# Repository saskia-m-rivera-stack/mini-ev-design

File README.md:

# mini-ev-design
Custom PCB design for a mini, remote-control electric car

Overview

The Mini Electric Vehicle (EV) Platform is a compact, battery-powered robotics platform designed to demonstrate embedded systems, motor control, and PCB design concepts. The project uses an ESP32 microcontroller and a DRV8833 dual H-bridge motor driver to control a brushed DC motor from a rechargeable LiPo battery.

This project was designed in KiCad as a custom PCB and serves as a learning platform for:

DC motor control using PWM
H-bridge motor drivers
Battery-powered embedded systems
Power distribution and decoupling
Wireless control using ESP32 Wi-Fi or Bluetooth
PCB schematiclayout

Features
ESP32-based control system
DRV8833 motor driver
Single brushed DC motor support
3.7V LiPo battery operation
On-board power regulation
Reverse polarity protection
Fuse protection
Decoupling and bulk capacitance for power stability
Expandable for sensors and remote-control functionality

System Architecture
Power System
The vehicle is powered by a 3.7V LiPo battery with integrated protection circuitry.

Power path:
Battery → Power Switch → Fuse → Buck Converter → 5V Rail

The 5V rail powers:
ESP32 Development Module
DRV8833 VM supply

All devices share a common ground.

Motor Control
The ESP32 generates PWM and direction signals that are connected to the DRV8833.

Control signals:
AIN1
AIN2
nSLEEP

Motor outputs:
AOUT1
AOUT2

The motor connects directly between AOUT1 and AOUT2.

No external flyback diode is required because the DRV8833 includes internal MOSFET body diode protection and current recirculation paths.

Power Integrity
DRV8833

Required capacitors:

100 µF bulk capacitor between VM and GND
0.1 µF ceramic capacitor between VM and GND
2.2 µF capacitor between VINT and GND
VCP capacitor according to datasheet recommendations
ESP32

10–47 µF bulk capacitor between 5V and GND
0.1 µF ceramic capacitor between 5V and GND
Battery Protection

Protection mechanisms include:

LiPo battery protection circuit (PCM)
PCB fuse protection
Optional ideal-diode MOSFET reverse polarity protection

Bill of Materials
ESP32 DevKitM-1 C3	Main microcontroller
DRV8833	Dual H-bridge motor driver
3V Brushed DC Motor	Vehicle propulsion
3.7V LiPo Battery	Main power source
Buck Converter	Generates regulated 5V rail
Fuse (3A)	Overcurrent protection
Capacitors	Decoupling and bulk filtering
Power Switch	System on/off control
JST Battery Connector	Battery connection

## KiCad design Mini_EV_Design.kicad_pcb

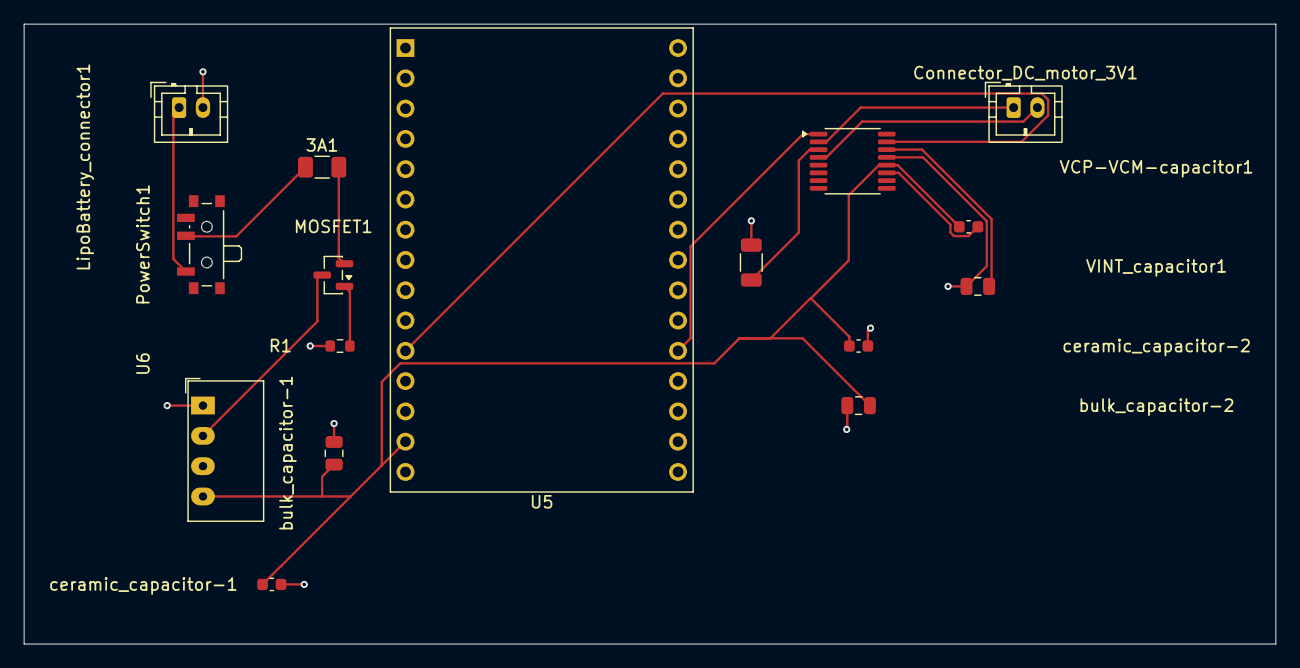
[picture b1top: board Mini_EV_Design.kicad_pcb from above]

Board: 4 copper layers, 105.0 x 52.0 mm, 16 parts (0 on the bottom side), 15 nets.

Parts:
3A1: Fuse; Fuse_1206_3216Metric
Connector_DC_motor_3V1: Conn_01x02; JST_PH_B2B-PH-K_1x02_P2.00mm_Vertical
LipoBattery_connector1: Conn_01x02; JST_PH_B2B-PH-K_1x02_P2.00mm_Vertical
MOSFET1: AO3401A; SOT-23
PowerSwitch1: SW_SPST; SW_SPDT_PCM12
R1: 100kΩ; R_0603_1608Metric
Resistor-current_sensing1: 0.1Ω; R_1206_3216Metric
U3: DRV8833PW; TSSOP-16_4.4x5mm_P0.65mm
U5: ESP32-C3-DevKitM-1
U6: CRE1S1205SC; Converter_DCDC_Murata_CRE1xxxxxxSC_THT
VCP-VCM-capacitor1: 0.01μF; C_0603_1608Metric
VINT_capacitor1: 2.2μF; C_0805_2012Metric
bulk_capacitor-1: 10μF; C_0805_2012Metric
bulk_capacitor-2: 100µF; C_0805_2012Metric
ceramic_capacitor-1: 0.1µF; C_0603_1608Metric
ceramic_capacitor-2: 0.1μF; C_0603_1608Metric

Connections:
GND: LipoBattery_connector1.2, R1.1, Resistor-current_sensing1.2, U3.13 (GND), U5.1 (GND), U5.6 (GND), U5.8 (GND), U5.12 (GND), U5.15 (GND), U5.16 (GND), U5.19 (GND), U5.24 (GND), U5.27 (GND), U5.30 (GND), U6.1 (-VIN), U6.3 (-VOUT), VINT_capacitor1.1, bulk_capacitor-1.1, bulk_capacitor-2.1, ceramic_capacitor-1.2, ceramic_capacitor-2.2
unnamed: Connector_DC_motor_3V1.1, U3.2 (AOUT1)
unnamed: Connector_DC_motor_3V1.2, U3.4 (AOUT2)
unnamed: LipoBattery_connector1.1, PowerSwitch1.1 (A)
unnamed: MOSFET1.3 (D), U6.2 (+VIN)
unnamed: MOSFET1.1 (G), R1.2
unnamed: 3A1.2, MOSFET1.2 (S)
unnamed: 3A1.1, PowerSwitch1.2 (B)
unnamed: U3.16 (AIN1), U5.26 (IO9)
unnamed: U3.15 (AIN2), U5.11 (IO10)
unnamed: Resistor-current_sensing1.1, U3.3 (AISEN)
unnamed: U3.11 (VCP), VCP-VCM-capacitor1.2
unnamed: U3.14 (VINT), VINT_capacitor1.2
unnamed: U3.12 (VM), U5.13 (5V), U5.14 (5V), U6.4 (+VOUT), VCP-VCM-capacitor1.1, bulk_capacitor-1.2, bulk_capacitor-2.2, ceramic_capacitor-1.1, ceramic_capacitor-2.1
unnamed: U3.1 (~SLEEP), U5.20 (IO4)

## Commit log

2026-05-29 Schematic and PCB files - KiCad
    .kicad_sch and .kicad_pcb
